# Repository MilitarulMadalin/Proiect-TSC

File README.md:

# InkTime

## Cuprins

1. [Schemă bloc](#1-schemă-bloc)
2. [Bill of Materials (BOM)](#2-bill-of-materials-bom)
3. [Descrierea hardware detaliată](#3-descrierea-hardware-detaliată)
4. [Mapare pini nRF52840](#4-mapare-pini-nrf52840)
5. [Design log](#5-decizii-de-design)

---

## 1. Schemă bloc

```
                  +--------------+      +-------------+
                  |   E-Paper    |      |    LiPo     |
                  |  Drive Circ. |      |   Charger   +
                  +------+-------+      +------+------+
                         |                     |
                         | EPD_PINS            | I2C, PMIC_INT       +-----------+
                         v                     |                     |   Fuel    |
  +-----------+   +--------------+             |            I2C      |   Gauge   |
  |  E-Paper  |<--+   E-Paper    |             |        +----------->|           |
  |   1.5"    |   |    Conn.     |             |        |            +-----------+
  +-----------+   +------+-------+             |        |
                         |                     |        |            +-----------+
                         |  SPI                |        |            |   USB-C   |
                         v                     v        |            |    J4     |
                  +----------------------------+--------+------+     +-----+-----+
                  |                                            |           |
                  |              nRF52840   (U1)               |<----------+
                  |                                            |  D+, D-
                  |                                            |<--------+
                  +--+--------+--------+--------+------+-------+         |
                     |        |        |        |      |                 |
                     | I2C    | I2C    | ANT1   | SWD  | 3xGPIO          | D+, D-
                     |        | HAPT.  |        |      |                 |
                     v        | EN     v        v      v           +-----+-----+
                  +-------+   |   +--------+ +-----+ +---------+   |    ESD    |
                  |  IMU  |   |   | Antena | | SWD | | Butoane |   | Protection|
                  |BMA423 |   |   |  2.4   | | J2  | +---------+   +-----------+
                  +-------+   |   +--------+ +-----+
                              v
                          +-------+
                          |Haptic |
                          |DRV2605|
                          +-------+
```

---

## 2. Bill of Materials (BOM)

| Desig. (ref.)                                                                  | Valoare / Part Number          | Funcție în circuit                           | Pachet        | Cant. | JLCPCB                                           | Datasheet                                                                                         |
|--------------------------------------------------------------------------------|--------------------------------|----------------------------------------------|---------------|-------|--------------------------------------------------|---------------------------------------------------------------------------------------------------|
| U1                                                                             | nRF52840-QIAA                  | MCU BLE 5 / 2.4 GHz, Cortex-M4F, 1 MB Flash  | aQFN73        | 1     | [C190794](https://jlcpcb.com/partdetail/C190794) | [PDF](https://infocenter.nordicsemi.com/pdf/nRF52840_PS_v1.7.pdf)                                 |
| IC1                                                                            | BQ25180YBGR                    | Încărcător LiPo 1-cell, programabil I2C      | DSBGA-8 0.4mm | 1     | [C965556](https://jlcpcb.com/partdetail/C965556) | [PDF](https://www.ti.com/lit/ds/symlink/bq25180.pdf)                                              |
| U3                                                                             | MAX17048G+T10                  | Fuel gauge ModelGauge 1-cell, I2C            | TDFN-8        | 1     | [C129977](https://jlcpcb.com/partdetail/C129977) | [PDF](https://www.analog.com/media/en/technical-documentation/data-sheets/MAX17048-MAX17049.pdf) |
| IC9                                                                            | RT6160AWSC                     | Buck-Boost 3V3, 2A (rail principal)          | WL-CSP-15     | 1     | [C58559](https://jlcpcb.com/partdetail/C58559)   | [PDF](https://www.richtek.com/assets/product_file/RT6160A/DS6160A-02.pdf)                         |
| IC3                                                                            | BMA423                         | Accelerometru 3-axis, step counter, wrist-tilt | LGA-12      | 1     | [C553690](https://jlcpcb.com/partdetail/C553690) | [PDF](https://www.bosch-sensortec.com/media/boschsensortec/downloads/datasheets/bst-bma423-ds000.pdf) |
| IC2                                                                            | DRV2605YZFR                    | Driver haptic ERM/LRA, 123 efecte, I2C       | DSBGA-9       | 1     | [C92482](https://jlcpcb.com/partdetail/C92482)   | [PDF](https://www.ti.com/lit/ds/symlink/drv2605.pdf)                                              |
| Q1                                                                             | DMG2305UX-7 (20V/4.2A)         | P-MOSFET load-switch rail EPD                | SOT-23        | 1     | [C114005](https://jlcpcb.com/partdetail/C114005) | [PDF](https://www.diodes.com/assets/Datasheets/DMG2305UX.pdf)                                     |
| Q3                                                                             | SI1308EDL-T1-GE3               | N-MOSFET pentru boost charge-pump EPD        | SOT-23        | 1     | [C294574](https://jlcpcb.com/partdetail/C294574) | [PDF](https://www.vishay.com/docs/66632/si1308edl.pdf)                                            |
| D3                                                                             | USBLC6-2SC6Y                   | TVS diode array, protecție ESD pe USB D±     | SOT-23-6      | 1     | [C7519](https://jlcpcb.com/partdetail/C7519)     | [PDF](https://www.st.com/resource/en/datasheet/usblc6-2.pdf)                                      |
| D2, D4, D5                                                                     | MBR0530                        | Diodă Schottky 30V pentru charge-pump EPD    | SOD-123       | 3     | [C131850](https://jlcpcb.com/partdetail/C131850) | [PDF](https://www.onsemi.com/pdf/datasheet/mbr0520-d.pdf)                                         |
| ANT1                                                                           | 2450AT18B100E                  | Antenă ceramică chip 2.4 GHz, Johanson       | 3216          | 1     | [C76907](https://jlcpcb.com/partdetail/C76907)   | [PDF](https://www.johansontechnology.com/datasheets/2450AT18B100E.pdf)                            |
| X1                                                                             | NX2016SA 32 MHz ±10 ppm        | Cristal HF pentru radio și CPU               | 2016          | 1     | [C255982](https://jlcpcb.com/partdetail/C255982) | [PDF](https://www.ndk.com/images/products/catalog/c_NX2016SA-STD-CRA-2_e.pdf)                     |
| X2                                                                             | ABS07-120 32.768 kHz           | Cristal LF pentru RTC (low-power)            | 3215          | 1     | [C32346](https://jlcpcb.com/partdetail/C32346)   | [PDF](https://abracon.com/Resonators/abs07-120.pdf)                                               |
| L1                                                                             | 3.9 nH                         | RF match filtru π — inductor serie antenă    | 0402          | 1     | [C1789](https://jlcpcb.com/partdetail/C1789)     | —                                                                                                 |
| L3                                                                             | 15 nH                          | RF match filtru π — inductor paralel          | 0402          | 1     | [C1794](https://jlcpcb.com/partdetail/C1794)     | —                                                                                                 |
| L2                                                                             | 10 µH                          | DCDC intern nRF52840 (pin DCC)               | 0402          | 1     | [C1046](https://jlcpcb.com/partdetail/C1046)     | —                                                                                                 |
| L5                                                                             | WE-TPC 744043680, 68 µH        | Boost e-paper (rail VGH / VGL)                | 4828          | 1     | [C492815](https://jlcpcb.com/partdetail/C492815) | [PDF](https://www.we-online.com/catalog/datasheet/744043680.pdf)                                  |
| L7                                                                             | FTC252012SR47MBCA, 0.47 µH     | Inductor putere pentru RT6160                 | 2520          | 1     | [C123046](https://jlcpcb.com/partdetail/C123046) | —                                                                                                 |
| J4                                                                             | KH-TYPE-C-16P                  | Conector USB-C receptacle (16 pini)           | SMT           | 1     | [C165948](https://jlcpcb.com/partdetail/C165948) | —                                                                                                 |
| J1                                                                             | Molex 503480-2400              | Conector baterie LiPo, 2-pin pitch 1.5 mm     | SMT           | 1     | [C518439](https://jlcpcb.com/partdetail/C518439) | [PDF](https://www.molex.com/pdm_docs/sd/5034802400_sd.pdf)                                        |
| J2                                                                             | TC2030-IDC (Tag-Connect)       | Footprint debug SWD (pogo-pins, fără receptacle) | —         | 1     | (doar footprint)                                 | [PDF](https://www.tag-connect.com/wp-content/uploads/bsk-pdf-manager/TC2030-IDC.pdf)              |
| SW_UP, SW_DN, SW_ENT                                                           | EVP-AKE31A                     | Buton tactil side-push 4.5×3.5 mm             | SMT           | 3     | [C719888](https://jlcpcb.com/partdetail/C719888) | [PDF](https://industrial.panasonic.com/cdbs/www-data/pdf/ATV0000/ATV0000CE11.pdf)                 |
| C11, C12                                                                       | 100 nF / 10V (X7R)             | Decuplare locală IC-uri digitale             | 0201          | 2     | [C106250](https://jlcpcb.com/partdetail/C106250) | —                                                                                                 |
| C5, C7, C8                                                                     | 100 µF / 6.3V                  | Bulk buck-boost RT6160                       | 0201          | 3     | [C19702](https://jlcpcb.com/partdetail/C19702)   | —                                                                                                 |
| C19                                                                            | 100 µF / 6.3V                  | Bulk rail VBAT                               | 0201          | 1     | [C19702](https://jlcpcb.com/partdetail/C19702)   | —                                                                                                 |
| C6, C14, C20, C21                                                              | 4.7 µF / 10V (X7R)             | Decuplare nRF (DEC*)                         | 0201          | 4     | [C19666](https://jlcpcb.com/partdetail/C19666)   | —                                                                                                 |
| C15                                                                            | 1.0 µF / 10V                   | Decuplare VREG nRF                           | 0201          | 1     | [C15849](https://jlcpcb.com/partdetail/C15849)   | —                                                                                                 |
| C39                                                                            | 10 µF / 6.3V                   | Bulk IC1 (charger)                           | 0201          | 1     | [C15850](https://jlcpcb.com/partdetail/C15850)   | —                                                                                                 |
| C43                                                                            | 4.7 µF                         | Intrare IC2 (driver haptic)                  | 0201          | 1     | [C19666](https://jlcpcb.com/partdetail/C19666)   | —                                                                                                 |
| C1-EP-DR, C24                                                                  | 10 µF                          | Filtre intrare driver EPD / RT6160           | 0201          | 2     | [C15850](https://jlcpcb.com/partdetail/C15850)   | —                                                                                                 |
| C2-EP-DR                                                                       | 4.7 µF / 25V                   | Bulk intrare boost EPD                       | 0201          | 1     | [C19666](https://jlcpcb.com/partdetail/C19666)   | —                                                                                                 |
| C25, C33                                                                       | 22 µF                          | Ieșire RT6160 (3V3)                          | 0201          | 2     | [C45783](https://jlcpcb.com/partdetail/C45783)   | —                                                                                                 |
| C17, C18                                                                       | 12 µF                          | Filtre DCDC intern nRF                       | 0201          | 2     | [C162698](https://jlcpcb.com/partdetail/C162698) | —                                                                                                 |
| C16                                                                            | 47 nF                          | Filtru control-loop RT6160                   | 0201          | 1     | [C113010](https://jlcpcb.com/partdetail/C113010) | —                                                                                                 |
| C9                                                                             | 820 pF                         | Decuplare DEC6 nRF                           | 0201          | 1     | [C1603](https://jlcpcb.com/partdetail/C1603)     | —                                                                                                 |
| C1, C2                                                                         | 12 pF (NP0 / C0G)              | Load-caps pentru X1 (32 MHz)                 | 0201          | 2     | [C1570](https://jlcpcb.com/partdetail/C1570)     | —                                                                                                 |
| C3, C4                                                                         | 1 pF                           | RF match (π) — shunt                         | 0201          | 2     | [C1552](https://jlcpcb.com/partdetail/C1552)     | —                                                                                                 |
| C10, C13, C22                                                                  | N.C. (Not Connected)           | Rezervate — neplasate la fabricație          | 0201          | 3     | (nu se lipește)                                  | —                                                                                                 |
| C23, C27, C29, C30, C31, C32, C34, C37, C38, C42                               | GRM011R60J152KE01L, 1.5 nF     | Filtre RF / bypass high-freq                 | 0201          | 10    | [C400827](https://jlcpcb.com/partdetail/C400827) | [PDF](https://www.murata.com/en-us/products/productdata/8796840689694/GCM155C71A225KE36-01A.pdf)  |
| EPD_C1, EPD_C2, EPD_C6, EPD_C7, EPD_C8, EPD_C9, EPD_C10, EPD_C11, EPD_C12      | 1 µF / 50V (X7R)               | Flying caps charge-pump pentru VGH/VGL       | 0201          | 9     | [C105948](https://jlcpcb.com/partdetail/C105948) | —                                                                                                 |
| EPD_C5                                                                         | 0.1 µF / 50V                   | Decuplare driver EPD                          | 0201          | 1     | [C14663](https://jlcpcb.com/partdetail/C14663)   | —                                                                                                 |
| R1_USB, R2_USB                                                                 | 5.1 kΩ 1% (CC1 / CC2)           | Pull-down USB-C — configurare device UFP     | 0201          | 2     | [C98220](https://jlcpcb.com/partdetail/C98220)   | —                                                                                                 |
| R1_EP_DR, R2_EP_DR                                                             | 10 kΩ 1%                       | Divider / gate pull pentru boost EPD         | 0201          | 2     | [C25744](https://jlcpcb.com/partdetail/C25744)   | —                                                                                                 |
| R_PWR_EPD, R_TYPE_SEL                                                          | 10 kΩ 1%                       | Selector tip panou EPD / enable rail         | 0201          | 2     | [C25744](https://jlcpcb.com/partdetail/C25744)   | —                                                                                                 |
| R2, R3, R4                                                                     | 0 Ω                            | Jumperi / pull-uri I2C (SDA, SCL, ALERT)     | 0201          | 3     | [C17168](https://jlcpcb.com/partdetail/C17168)   | —                                                                                                 |
| R5, R7, R8                                                                     | 10 kΩ 1%                       | Pull-up butoane SW_UP, SW_DN, SW_ENT         | 0201          | 3     | [C25744](https://jlcpcb.com/partdetail/C25744)   | —                                                                                                 |
| R9                                                                             | 10 kΩ 1%                       | MR (TS / mode-select) pe BQ25180             | 0201          | 1     | [C25744](https://jlcpcb.com/partdetail/C25744)   | —                                                                                                 |
| R17, R18                                                                       | 3.3 kΩ 1%                      | Feedback / setare tensiune RT6160            | 0201          | 2     | [C22975](https://jlcpcb.com/partdetail/C22975)   | —                                                                                                 |
| TP_3V3, TP_3.3V, TP_VREG, TP_VBAT, TP_BAT_GND, TP_GND, TP_RESET, TP_SDA, TP_SCL, TP_SWDCLK, TP_SWDIO, TP_SWO, TP_ON, TP_OP | Pad 20 mil               | Puncte de test pentru măsurători / debug     | 20R pad       | 14    | (doar footprint)                                 | —                                                                                                 |
| SJ1                                                                            | Solder jumper                  | Select hardware (bootloader / mod)            | 0201 jumper   | 1     | (doar footprint)                                 | —                                                                                                 |

### Off-board

| Componentă          | Valoare / Model                      | Legătură                                   |
|---------------------|--------------------------------------|--------------------------------------------|
| Baterie             | LiPo 483450, 3.7V, 2400 mAh          | Conector J1 (Molex 503480-2400)            |
| Panou e-paper       | GDEW0154M09, 1.54" 200×200 px, SPI   | Conector FPC 24 pini (nu e pe placă — se leagă prin cablaj) |
| Motor vibrație      | ERM 10×2.7 mm, 3V nominal            | Pini OUT+ / OUT− ai DRV2605                |

---

## 3. Descrierea hardware detaliată

### 3.1. Alimentare

Lanțul de alimentare respectă o arhitectură clasică **charger → baterie → regulator**, adaptată pentru low-power:

1. **Intrare USB-C (J4)** — 5V / max 500 mA. Liniile D+/D− sunt protejate de **USBLC6-2 (D3)**, diodă TVS cu capacitate mică care nu afectează eye-pattern-ul USB 2.0 Full-Speed.
2. **Încărcător BQ25180 (IC1)** — integrează charger liniar 1-cell LiPo cu până la 500 mA, path management, detecție over-voltage 18V și **ship-mode**. Configurabil pe I2C: curent de încărcare, prag de terminare, temperatură. Pinul **INT** este conectat la nRF pentru evenimente.
3. **Baterie LiPo 2400 mAh** conectată la J1. Pinul TS/MR al BQ25180 nu folosește termistor.
4. **Fuel gauge MAX17048 (U3)** — măsoară direct tensiunea bateriei cu algoritmul **ModelGauge**, oferind SoC și rata de descărcare. Pinul ALERT este rutat la nRF pentru notificări de low-battery.
5. **Buck-Boost RT6160 (IC9)** — convertor **step-up/step-down** la **3V3 fix**, eficiență până la 95%. Alegerea unui buck-boost e critică: o baterie LiPo ajunge la ~3.0V la descărcare, iar un LDO ar avea dropout, în timp ce un buck pur nu ar putea menține 3V3 când bateria e sub acest nivel. RT6160 oferă continuitate până la ~2.5V cu regulare menținută.
6. **Load-switch Q1 (DMG2305UX-7)** — P-MOSFET care deconectează complet rail-ul boost al e-paper-ului în stand-by.

**Rețeaua RF**: antena ceramică ANT1 e alimentată prin **filtru π** pentru match la 50 Ω și filtrare armonici. Traseul de la pinul **ANT** al nRF la antenă respectă **controlled impedance** 50 Ω.

### 3.2. Microcontroller și clock

**nRF52840** rulează cu două cristale:

- **X1 = 32 MHz (NX2016SA)** pe pinii XC1/XC2, cristal principal pentru radio și HFCLK. Toleranță ≤ 40 ppm.
- **X2 = 32.768 kHz (ABS07)** pe pinii P0.00/XL1, P0.01/XL2, clock low-power pentru RTC și sleep. Toleranță 20 ppm, consum < 1 µA.

Decuplarea rail-urilor interne folosește 4.7 µF + 100 nF + 1 µF + 100 pF conform reference design Nordic. **L4 + L6**împreună cu C14 + C15 + C20 implementează DC/DC intern care reduce consumul cu ~30% față de modul LDO.

### 3.3. Display e-paper

E-paper-ul **GDEW0154M09** are nevoie de patru rail-uri: +15V (VGH), −15V (VGL), +22V (VPP), −20V (VEE). Driver circuit-ul de pe Sheet 2 folosește:

- **Boost cu SI1308 + L5 + MBR0530** care generează VGH/VGL prin charge-pump multi-stage.
- **9× condensatori 1µF/50V** — flying caps pentru stagele charge-pump.

Controlul e pe SPI + semnale discrete: RST, BUSY, D/C, CS. Rail-ul EPD_3V3 se activează doar când se refresh-uiește display-ul; în rest, e-paper-ul menține imaginea fără alimentare.

### 3.4. Senzori și actuatori

- **BMA423 (IC3)** — accelerometru 3-axis 12-bit cu engine de pași, detecție tap/double-tap și wrist-tilt. Întreruperi: INT1, INT2. Interfața I2C, adresa 0x19.
- **DRV2605 (IC2)** — driver haptic pentru motoare ERM sau LRA. Conține **librărie pre-programată cu 123 efecte**, plus mod real-time. Activat prin HAPTIC_EN pentru a elimina complet consumul în idle. Bobina motorului e conectată la pinii OUT+/OUT−.

### 3.5. Butoane și debug

Cele 3 butoane sunt conectate GPIO cu GND, cu pull-up intern activat software. **Fără debounce hardware** , se face în firmware.

Conectorul **TC2030-IDC (J2)** e un footprint 6-pin fără receptacle fizic, debugger-ul are pogo-pins care fac contact direct pe PCB, economisind componenta și spațiu. Semnale: SWDIO, SWDCLK, SWO, RESET, 3V3, GND.

---

## 4. Mapare pini nRF52840

Mapare extrasă din schematic (InkTime v6, Sheet 1 + Sheet 2):

| Pin nRF52840    | Nume net       | Funcție firmware                | Destinație periferic          |
|-----------------|----------------|---------------------------------|-------------------------------|
| **Alimentare**  |                |                                 |                               |
| VDD / VDDH      | 3V3            | Alimentare digital              | Rail 3V3 (de la RT6160)        |
| VBUS            | VBUS           | Detecție USB plug-in            | USB 5V                         |
| DEC1..DEC6      | DEC*           | Decuplare internă               | Local 100 nF × 6               |
| DCC / DCCH      | LX1 / LX2      | DC-DC intern (SMPS)             | L4 + L6 (10 µH) + filtre      |
| **Clock**       |                |                                 |                               |
| P0.00 / XL1     | XL1            | Cristal RTC 32.768 kHz          | X2                             |
| P0.01 / XL2     | XL2            | Cristal RTC 32.768 kHz          | X2                             |
| XC1 / XC2       | XC1 / XC2      | Cristal HF 32 MHz               | X1                             |
| **Radio**       |                |                                 |                               |
| ANT             | RF             | Ieșire RF                       | filtru π → ANT1                |
| **USB**         |                |                                 |                               |
| D+              | D+             | USB 2.0 Full-Speed              | J4 (prin USBLC6-2)            |
| D-              | D-             | USB 2.0 Full-Speed              | J4 (prin USBLC6-2)            |
| **Debug**       |                |                                 |                               |
| SWDCLK          | SWDCLK         | Clock debug                     | J2 pin 4                       |
| SWDIO           | SWDIO          | Data debug                      | J2 pin 2                       |
| P0.18 / nRESET  | RESET          | Reset hardware                  | J2 pin 5 + TP_RESET           |
| **SPI (TWIM1)** — e-paper |      |                                 |                               |
| P0.13           | EPD_SCK / SCK  | Clock SPI                       | FPC pin 5                      |
| P0.14           | EPD_MOSI / MOSI| Data SPI master→slave           | FPC pin 4                      |
| P0.15           | EPD_CS         | Chip-select                     | FPC pin 6                      |
| P0.16           | EPD_DC         | Data / Command                  | FPC pin 7                      |
| P0.17           | EPD_RST        | Reset display                   | FPC pin 8                      |
| P0.19           | EPD_BUSY       | Busy-in (drive done)            | FPC pin 9                      |
| **I2C (TWIM0)** — senzori |      |                                 |                               |
| P0.24           | SDA            | I2C data                        | BMA423 · DRV2605 · MAX17048 · BQ25180 |
| P0.25           | SCL            | I2C clock                       | BMA423 · DRV2605 · MAX17048 · BQ25180 |
| **Întreruperi** |                |                                 |                               |
| P0.22           | IMU_INT1       | IMU: pași / tap                 | BMA423 pin 5                   |
| P0.23           | IMU_INT2       | IMU: wake-up                    | BMA423 pin 6                   |
| P0.20           | ALERT          | Fuel gauge low-bat              | MAX17048 pin 5                 |
| P0.21           | PMIC_INT       | Charger events                  | BQ25180 pin A1                 |
| **Butoane**     |                |                                 |                               |
| P0.04           | SW_UP          | Buton sus                       | SW_UP (push-to-GND)            |
| P0.05           | SW_DN          | Buton jos                       | SW_DN (push-to-GND)            |
| P0.06           | SW_ENT         | Buton enter                     | SW_ENT (push-to-GND)           |
| **Control**     |                |                                 |                               |
| P0.26           | HAPTIC_EN      | Enable DRV2605 + boost EPD     | IC2 pin EN / Q3 gate          |
| P0.27           | EPD_PWR        | Load-switch panou e-paper       | Q1 gate                        |

---

## 5. Decizii de design

- **Utilizarea componentelor SMD în capsule mici** Am ales respectarea strictă a dimensiunilor impuse (0201 pentru rezistențe și condensatoare ≤100nF, respectiv 0402 pentru valori mai mari) pentru a reduce dimensiunea totală a PCB-ului. Această alegere contribuie la integrarea mai ușoară în carcasă și la un design compact, esențial pentru dispozitive portabile.
- **Amplasarea componentelor doar pe layer-ul TOP** Toate componentele au fost plasate pe TOP pentru a simplifica procesul de asamblare și pentru a evita costuri suplimentare asociate montajului pe ambele fețe. În plus, această abordare reduce riscul de erori mecanice și facilitează inspecția vizuală.
- **Excluderea planului de masă sub antenă** Zona de sub antenă a fost complet decuplată de planul de masă și nu au fost rutate semnale acolo. Aceasta previne detunarea antenei și pierderile de eficiență, asigurând performanță RF optimă.
- **Silkscreen minimalist și lizibil** Am inclus doar denumirile componentelor pentru a evita aglomerarea vizuală. Un silkscreen curat ajută la identificarea rapidă a componentelor și îmbunătățește mentenanța.
- **Utilizarea unui PCB cu 4 layere** Am ales o structură pe 4 layere (TOP, GND plane, POWER plane, BOTTOM) pentru a îmbunătăți semnificativ integritatea semnalului și stabilitatea alimentării.

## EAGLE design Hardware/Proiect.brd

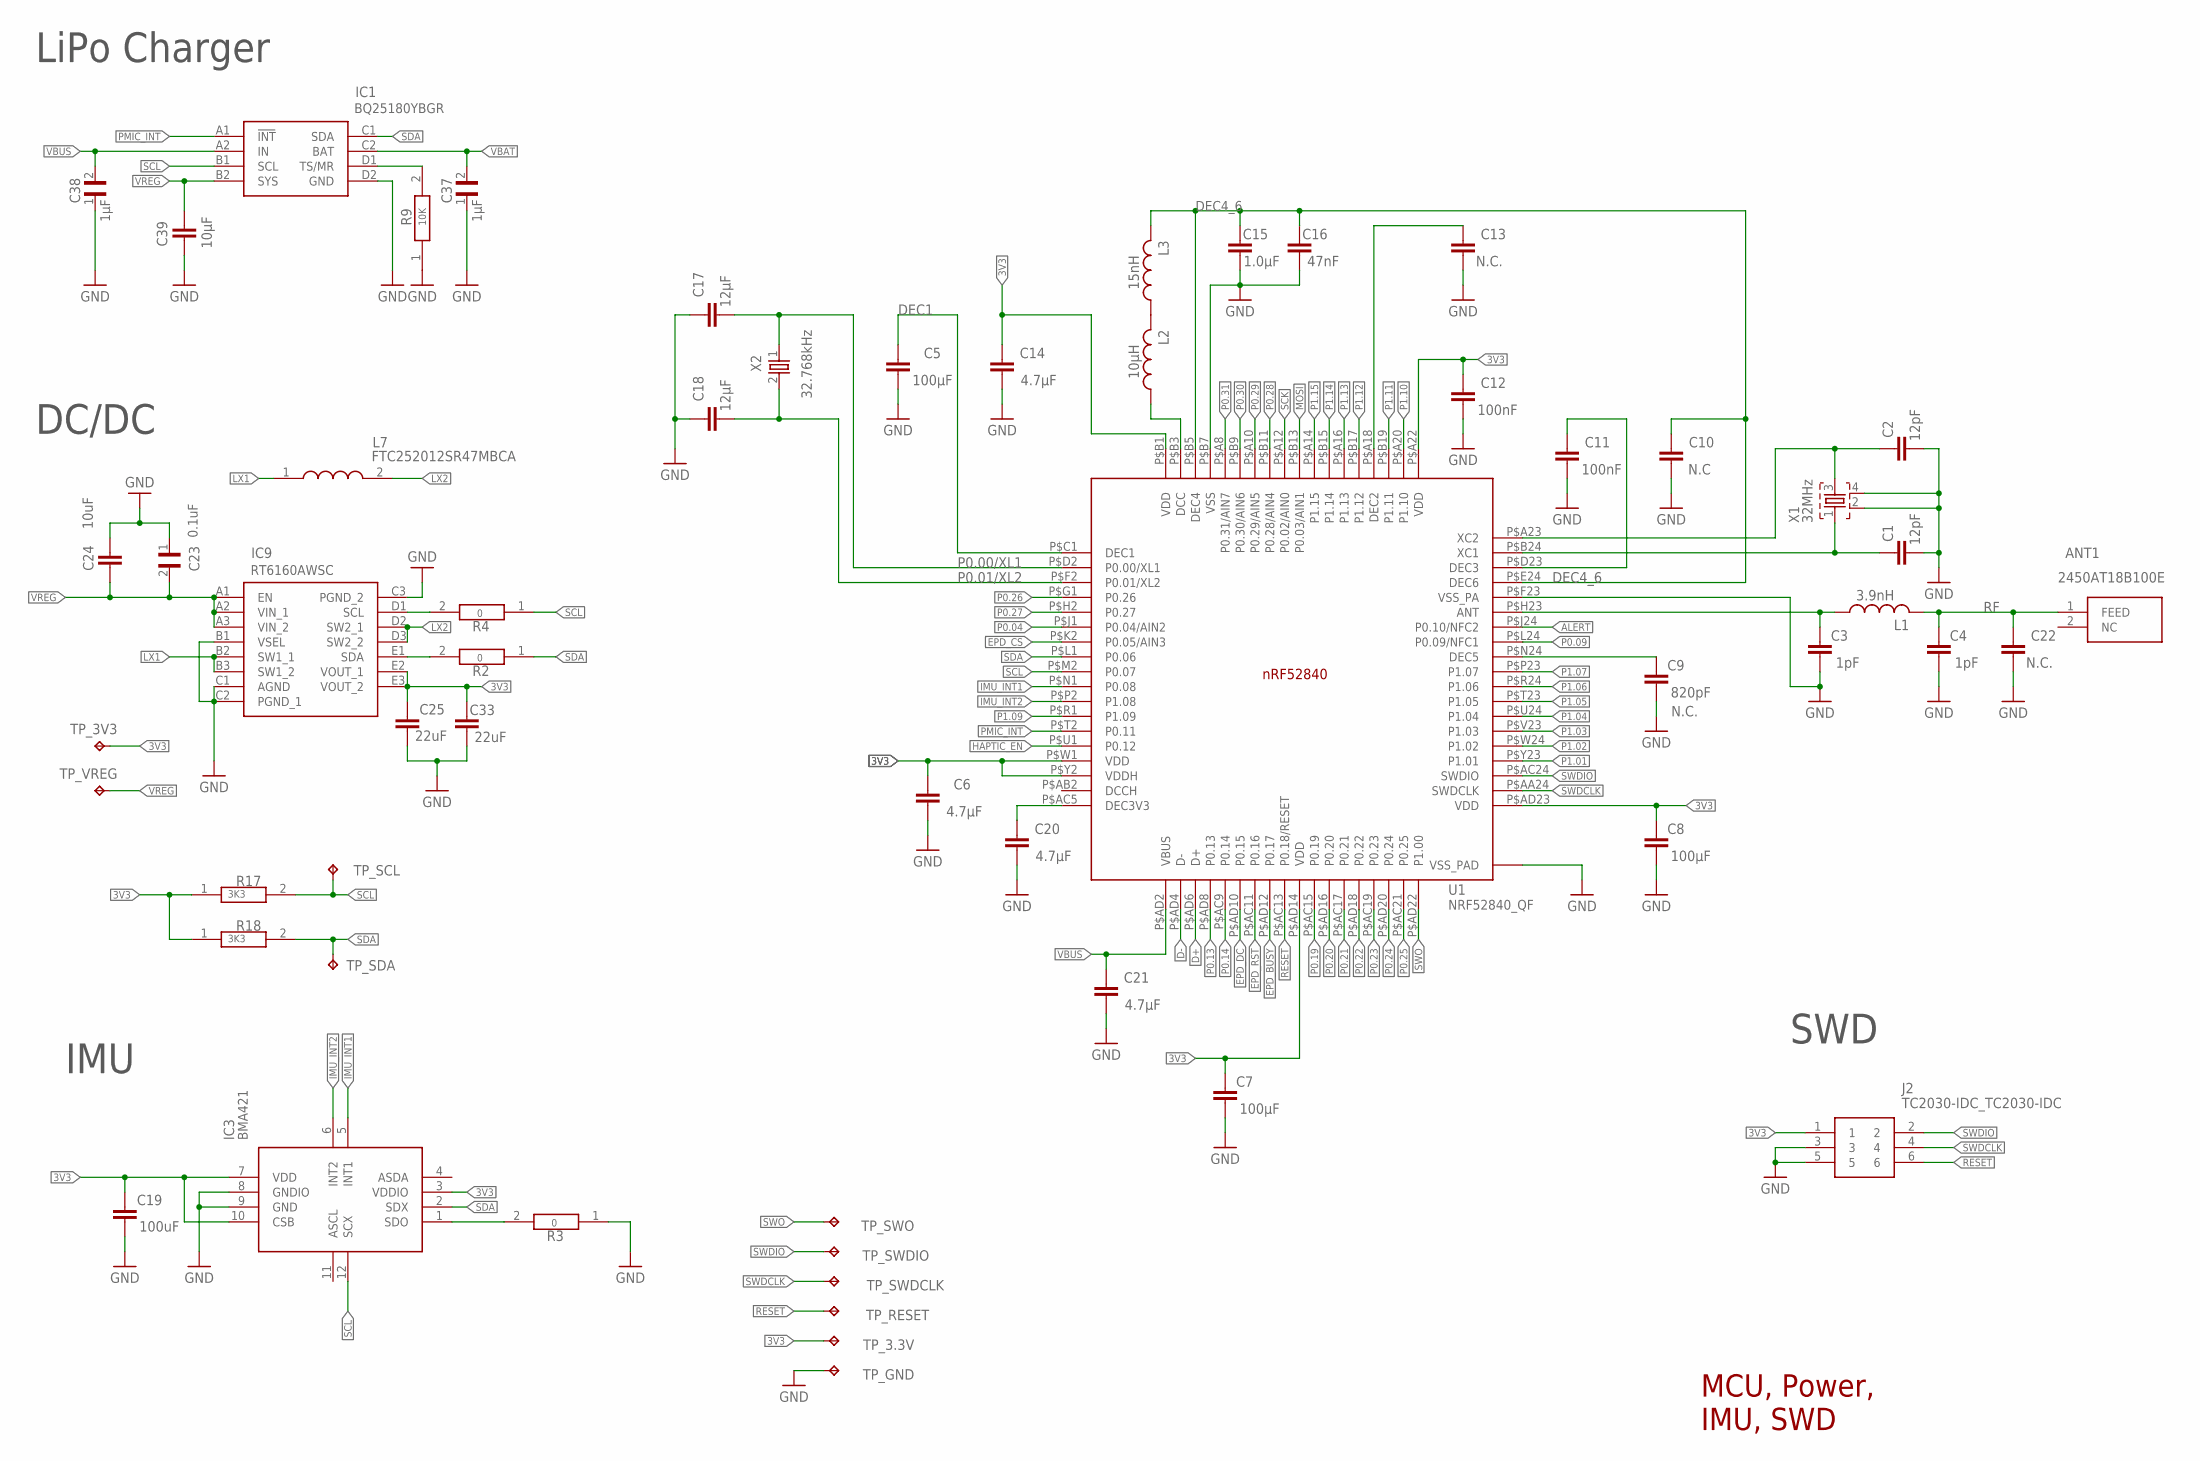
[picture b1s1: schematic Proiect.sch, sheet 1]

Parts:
ANT1: 2450AT18B100E_2450AT18B100E; 2450AT18B100E_ANTC3216X140N
C1, C2: 12pF; NORDIC_NRF_3_RESC0201_L
C3, C4: 1pF; NORDIC_NRF_3_RESC0201_L
C5, C7, C8: 100µF; NORDIC_NRF_3_RESC0201_L
C6, C14, C20, C21: 4.7µF; NORDIC_NRF_3_RESC0201_L
C9: 820pF; NORDIC_NRF_3_RESC0201_L
C10: N.C; NORDIC_NRF_3_RESC0201_L
C11, C12: 100nF; NORDIC_NRF_3_RESC0201_L
C13, C22: N.C.; NORDIC_NRF_3_RESC0201_L
C15: 1.0µF; NORDIC_NRF_3_RESC0201_L
C16: 47nF; NORDIC_NRF_3_RESC0201_L
C17, C18: 12µF; NORDIC_NRF_3_RESC0201_L
C19: 100uF; NORDIC_NRF_3_RESC0201_L
C23, C37, C38: GRM011R60J152KE01L_2_GRM011R60J152KE01L; GRM011R60J152KE01L_2_CAPC0201X13N
C24: 10uF; NORDIC_NRF_3_RESC0201_L
C25, C33: 22uF; NORDIC_NRF_3_RESC0201_L
C39: 10µF; NORDIC_NRF_3_RESC0201_L
IC1: BQ25180YBGR_BQ25180YBGR; BQ25180YBGR_BGA8C40P2X4_100X155X50
IC3: BMA423_BMA423
IC9: RT6160AWSC_RT6160AWSC; RT6160AWSC_BGA15C40P3X5_140X230X60
J2: TC2030-IDC_TC2030-IDC; TC2030-IDC_TC2030IDC
L1: 3.9nH; NORDIC_NRF_2_RESC0402_L
L2: 10µH; NORDIC_NRF_2_RESC0402_L
L3: 15nH; NORDIC_NRF_2_RESC0402_L
L7: MLP2016SR47MT0S1_FTC252012SR47MBCA; MLP2016SR47MT0S1_INDC2016X100N
R2, R3, R4, R9, R17, R18: ERA-1AEB3401C_CPF0201D7K68C1; ERA-1AEB3401C_0201
TP_3.3V, TP_3V3: HECTOR_WATCH_1_TPTP20R; HECTOR_WATCH_1_TP20R
TP_GND: HECTOR_WATCH_1_TPTP20R; HECTOR_WATCH_1_TP20R
TP_RESET: HECTOR_WATCH_1_TPTP20R; HECTOR_WATCH_1_TP20R
TP_SCL: HECTOR_WATCH_1_TPTP20R; HECTOR_WATCH_1_TP20R
TP_SDA: HECTOR_WATCH_1_TPTP20R; HECTOR_WATCH_1_TP20R
TP_SWDCLK: HECTOR_WATCH_1_TPTP20R; HECTOR_WATCH_1_TP20R
TP_SWDIO: HECTOR_WATCH_1_TPTP20R; HECTOR_WATCH_1_TP20R
TP_SWO: HECTOR_WATCH_1_TPTP20R; HECTOR_WATCH_1_TP20R
TP_VREG: HECTOR_WATCH_1_TPTP20R; HECTOR_WATCH_1_TP20R
U1: NORDIC_NRF_4_NRF52840_QF; NORDIC_NRF_4_AQFN50P700X700X85_HS-74N
X1: 32MHz; NORDIC_NRF_BT-XTAL_2016_N
X2: 32.768kHz; NORDIC_NRF_1_XTAL_3215_N

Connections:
3V3: C6.1, C7.1, C8.1, C12.1, C14.1, C19.1, C25.1, C33.1, IC3.3 (VDDIO), IC3.7 (VDD), IC3.10 (CSB), IC9.E2 (VOUT_1), IC9.E3 (VOUT_2), J2.1, R17.1, R18.1, TP_3.3V.TP, TP_3V3.TP, U1.P$A22 (VDD), U1.P$AD14 (VDD), U1.P$AD23 (VDD), U1.P$B1 (VDD), U1.P$W1 (VDD), U1.P$Y2 (VDDH); also elsewhere on the board
ALERT: U1.P$J24 (P0.10/NFC2); also elsewhere on the board
D+: U1.P$AD6 (D+); also elsewhere on the board
D-: U1.P$AD4 (D-); also elsewhere on the board
DEC1: C5.1, U1.P$C1 (DEC1)
DEC4_6: C10.1, C15.1, C16.1, L3.2, U1.P$B5 (DEC4), U1.P$E24 (DEC6)
EPD_BUSY: U1.P$AD12 (P0.17); also elsewhere on the board
EPD_CS: U1.P$K2 (P0.05/AIN3); also elsewhere on the board
EPD_DC: U1.P$AD10 (P0.15); also elsewhere on the board
EPD_RST: U1.P$AC11 (P0.16); also elsewhere on the board
GND: C1.2, C2.2, C3.2, C4.2, C5.2, C6.2, C7.2, C8.2, C9.2, C10.2, C11.2, C12.2, C13.2, C14.2, C15.2, C16.2, C17.1, C18.1, C19.2, C20.2, C21.2, C22.2, C23.1, C24.1, C25.2, C33.2, C37.1, C38.1, C39.2, IC1.D2 (GND), IC3.8 (GNDIO), IC3.9 (GND), IC9.B1 (VSEL), IC9.C1 (AGND), IC9.C2 (PGND_1), IC9.C3 (PGND_2), J2.3, J2.5, R3.1, R9.1, TP_GND.TP, U1.P$74 (VSS_PAD), U1.P$75 (VSS_PAD), U1.P$76 (VSS_PAD), U1.P$77 (VSS_PAD), U1.P$78 (VSS_PAD), U1.P$79 (VSS_PAD), U1.P$80 (VSS_PAD), U1.P$81 (VSS_PAD), U1.P$82 (VSS_PAD), U1.P$83 (VSS_PAD), U1.P$84 (VSS_PAD), U1.P$85 (VSS_PAD), U1.P$86 (VSS_PAD), U1.P$87 (VSS_PAD), U1.P$88 (VSS_PAD), U1.P$89 (VSS_PAD), U1.P$90 (VSS_PAD), U1.P$B7 (VSS), U1.P$F23 (VSS_PA), X1.2, X1.4; also elsewhere on the board
HAPTIC_EN: U1.P$U1 (P0.12); also elsewhere on the board
IMU_INT1: IC3.5 (INT1), U1.P$N1 (P0.08)
IMU_INT2: IC3.6 (INT2), U1.P$P2 (P1.08)
LX1: IC9.B2 (SW1_1), IC9.B3 (SW1_2), L7.1
LX2: IC9.D2 (SW2_1), IC9.D3 (SW2_2), L7.2
MOSI: U1.P$B13 (P0.03/AIN1); also elsewhere on the board
unnamed: IC3.1 (SDO), R3.2
unnamed: IC1.D1 (TS/MR), R9.2
unnamed: IC9.E1 (SDA), R2.2
unnamed: IC9.D1 (SCL), R4.2
unnamed: L2.1, U1.P$B3 (DCC)
unnamed: L2.2, L3.1
unnamed: C13.1, U1.P$A18 (DEC2)
unnamed: C9.1, U1.P$N24 (DEC5)
unnamed: C11.1, U1.P$D23 (DEC3)
unnamed: C3.1, L1.1, U1.P$H23 (ANT)
unnamed: C2.1, U1.P$A23 (XC2), X1.3
unnamed: C1.1, U1.P$B24 (XC1), X1.1
P0.00/XL1: C17.2, U1.P$D2 (P0.00/XL1), X2.1
P0.01/XL2: C18.2, U1.P$F2 (P0.01/XL2), X2.2
P0.04: U1.P$J1 (P0.04/AIN2)
P0.09: U1.P$L24 (P0.09/NFC1)
P0.13: U1.P$AD8 (P0.13); also elsewhere on the board
P0.14: U1.P$AC9 (P0.14); also elsewhere on the board
P0.19: U1.P$AC15 (P0.19)
P0.20: U1.P$AD16 (P0.20)
P0.21: U1.P$AC17 (P0.21)
P0.22: U1.P$AD18 (P0.22)
P0.23: U1.P$AC19 (P0.23)
P0.24: U1.P$AD20 (P0.24)
P0.25: U1.P$AC21 (P0.25)
P0.26: U1.P$G1 (P0.26)
P0.27: U1.P$H2 (P0.27)
P0.28: U1.P$B11 (P0.28/AIN4)
P0.29: U1.P$A10 (P0.29/AIN5)
P0.30: U1.P$B9 (P0.30/AIN6)
P0.31: U1.P$A8 (P0.31/AIN7)
P1.01: U1.P$Y23 (P1.01); also elsewhere on the board
P1.02: U1.P$W24 (P1.02); also elsewhere on the board
P1.03: U1.P$V23 (P1.03)
P1.04: U1.P$U24 (P1.04)
P1.05: U1.P$T23 (P1.05)
P1.06: U1.P$R24 (P1.06)
P1.07: U1.P$P23 (P1.07)
P1.09: U1.P$R1 (P1.09)
P1.10: U1.P$A20 (P1.10)
P1.11: U1.P$B19 (P1.11)
P1.12: U1.P$B17 (P1.12)
P1.13: U1.P$A16 (P1.13)
P1.14: U1.P$B15 (P1.14)
P1.15: U1.P$A14 (P1.15)
PMIC_INT: IC1.A1 (!INT), U1.P$T2 (P0.11)
RESET: J2.6, TP_RESET.TP, U1.P$AC13 (P0.18/RESET)
RF: ANT1.1 (FEED), C4.1, C22.1, L1.2
SCK: U1.P$A12 (P0.02/AIN0); also elsewhere on the board
SCL: IC1.B1 (SCL), IC3.12 (SCX), R4.1, R17.2, TP_SCL.TP, U1.P$M2 (P0.07); also elsewhere on the board
SDA: IC1.C1 (SDA), IC3.2 (SDX), R2.1, R18.2, TP_SDA.TP, U1.P$L1 (P0.06); also elsewhere on the board
SWDCLK: J2.4, TP_SWDCLK.TP, U1.P$AA24 (SWDCLK)
SWDIO: J2.2, TP_SWDIO.TP, U1.P$AC24 (SWDIO)
SWO: TP_SWO.TP, U1.P$AD22 (P1.00)
VBAT: C37.2, IC1.C2 (BAT); also elsewhere on the board
VBUS: C21.1, C38.2, IC1.A2 (IN), U1.P$AD2 (VBUS); also elsewhere on the board
VBUS/2.6D1: C20.1, U1.P$AC5 (DEC3V3)
VREG: C23.2, C24.2, C39.1, IC1.B2 (SYS), IC9.A1 (EN), IC9.A2 (VIN_1), IC9.A3 (VIN_2), TP_VREG.TP

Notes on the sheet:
LiPo Charger
MCU, Power, IMU, SWD
DC/DC
IMU
SWD

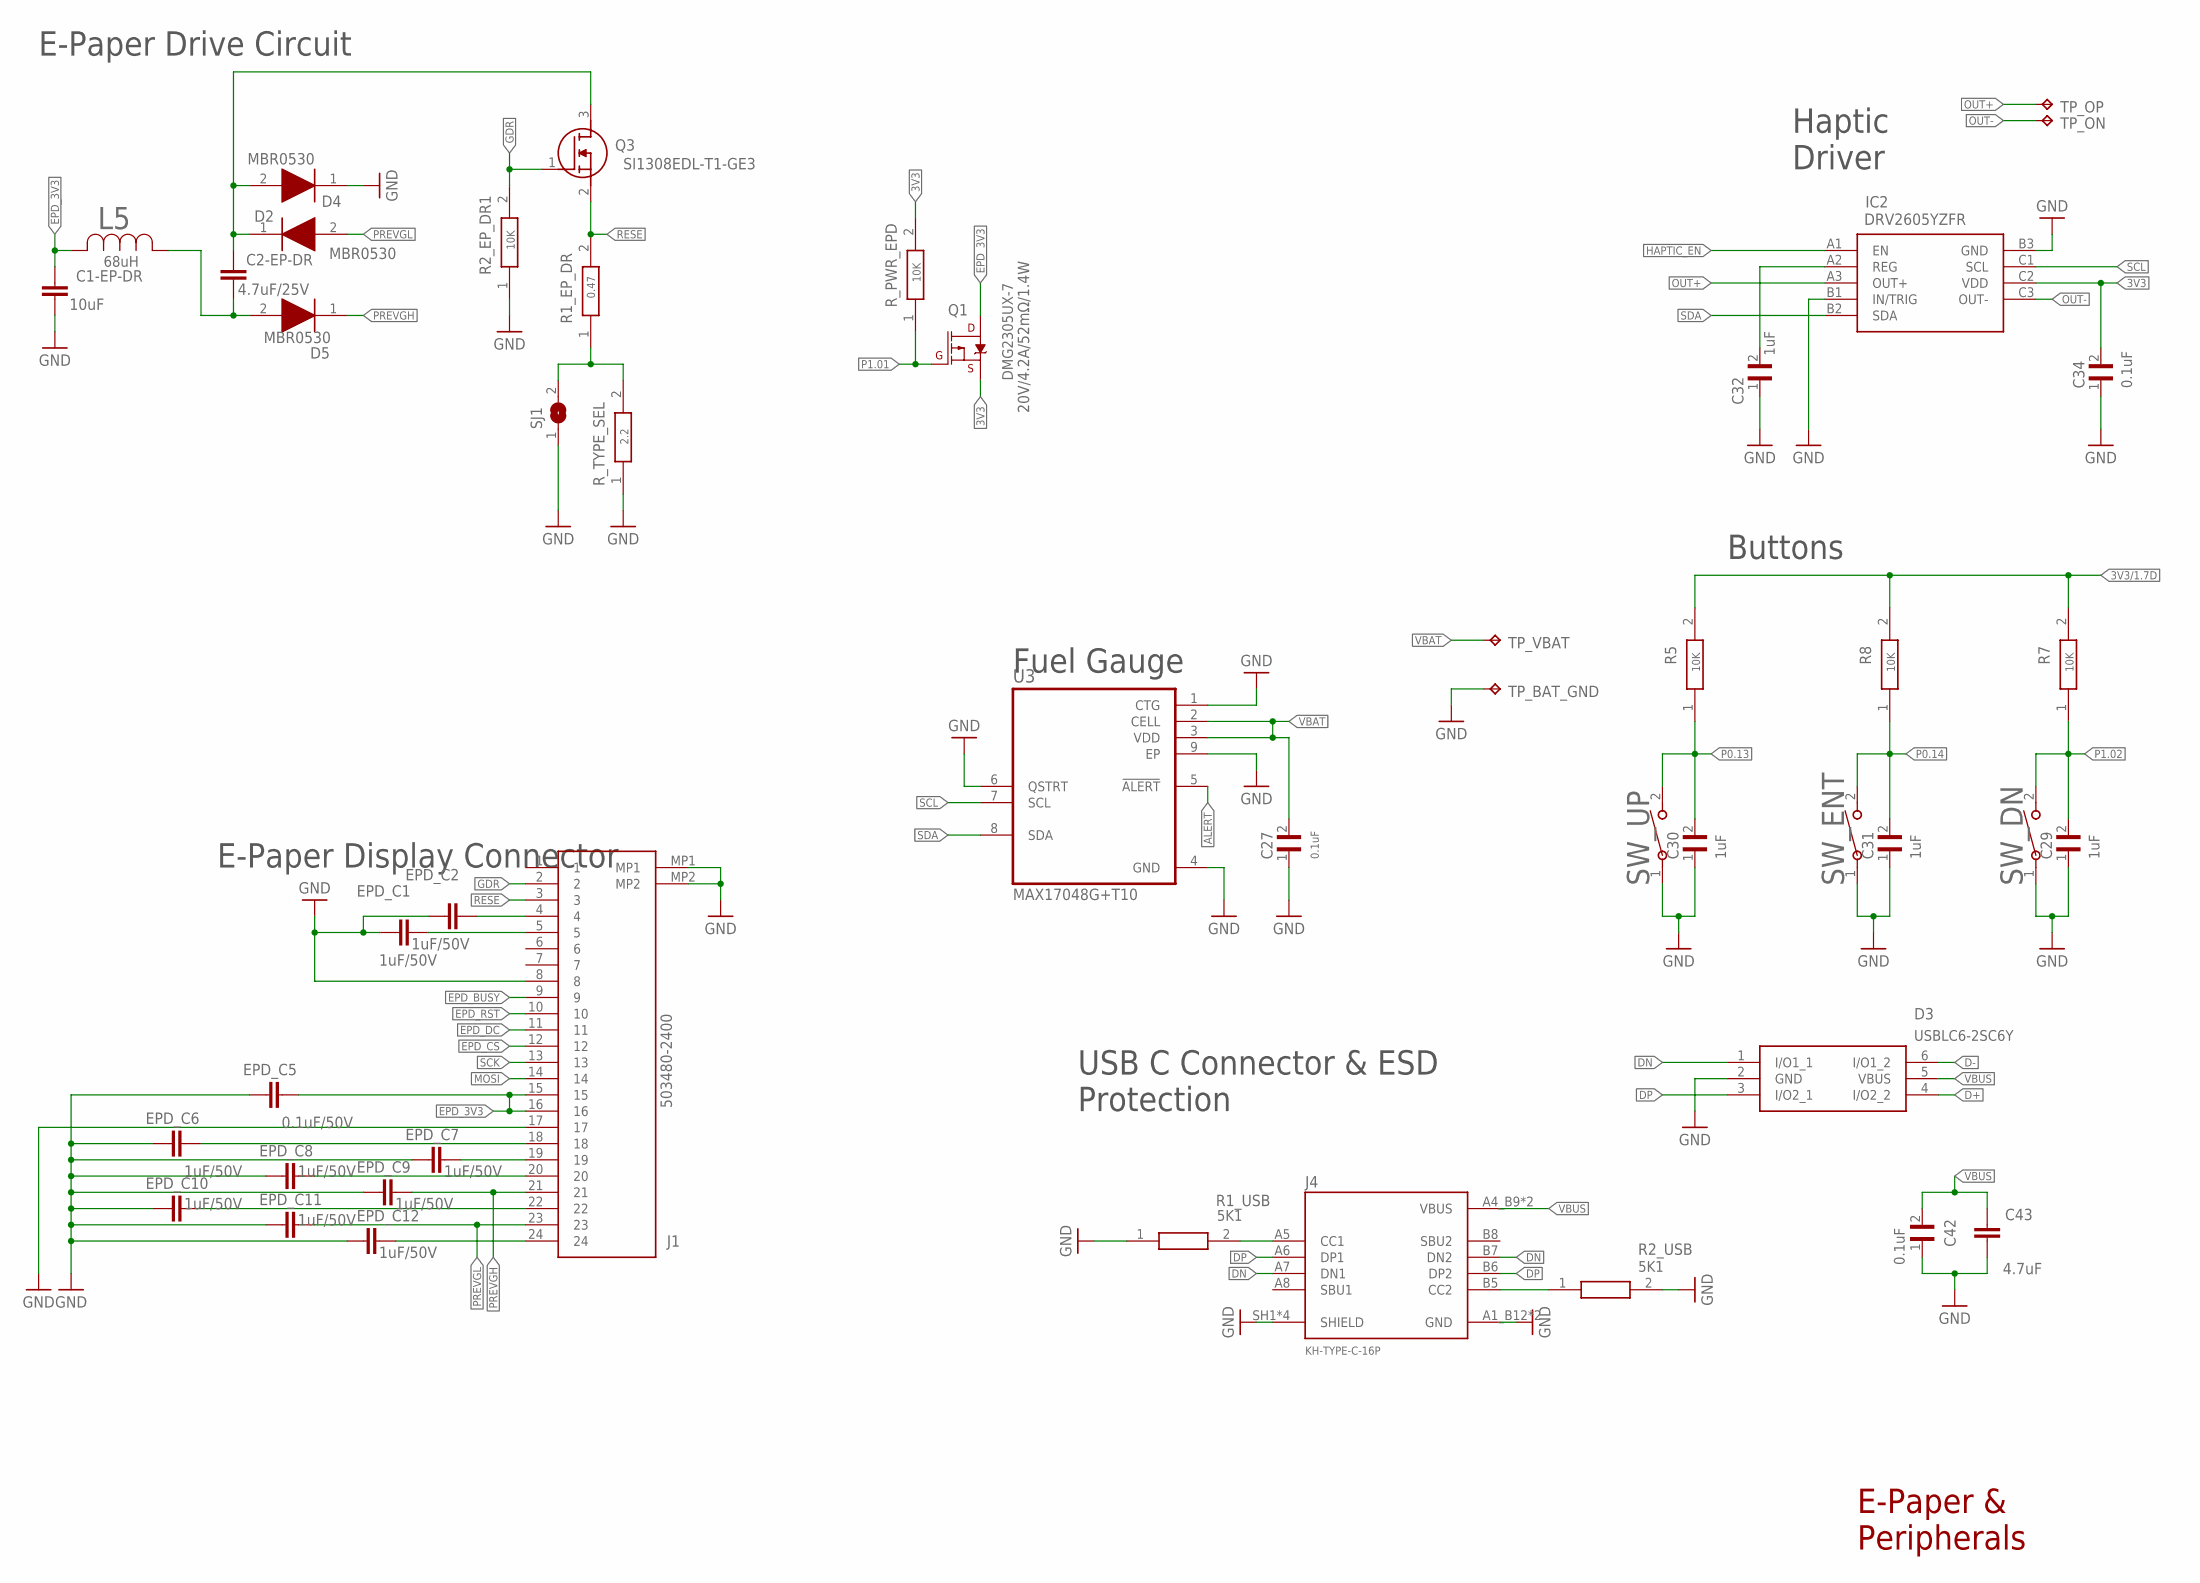
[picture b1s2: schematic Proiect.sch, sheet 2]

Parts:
C1-EP-DR: 10uF; NORDIC_NRF_3_RESC0201_L
C2-EP-DR: 4.7uF/25V; NORDIC_NRF_3_RESC0201_L
C27, C29, C30, C31, C32, C34, C42: GRM011R60J152KE01L_2_GRM011R60J152KE01L; GRM011R60J152KE01L_2_CAPC0201X13N
C43: 4.7uF; NORDIC_NRF_3_RESC0201_L
D2, D4, D5: ESP32_C6_LIBRARY_5_MBR0530; ESP32_C6_LIBRARY_5_SOD3716X135N
D3: ESP32_C6_LIBRARY_3_USBLC6-2SC6Y; ESP32_C6_LIBRARY_3_SOT95P280X145-6N
EPD_C1, EPD_C2, EPD_C6, EPD_C7, EPD_C8, EPD_C9, EPD_C10, EPD_C11, EPD_C12: 1uF/50V; NORDIC_NRF_3_RESC0201_L
EPD_C5: 0.1uF/50V; NORDIC_NRF_3_RESC0201_L
IC2: DRV2605YZFR_DRV2605YZFR; DRV2605YZFR_BGA9C50P3X3_144X144X62
J1: 503480-2400_503480-2400; 503480-2400_5034802400
J4: KH-TYPE-C-16P_KH-TYPE-C-16P; KH-TYPE-C-16P_KINGHELM_KH-TYPE-C-16P
L5: ESP32_C6_LIBRARY_2_744043680IND_4828-WE-TPC_WRE; ESP32_C6_LIBRARY_2_IND_4828-WE-TPC_WRE
Q1: 20V/4.2A/52mΩ/1.4W; ESP32_C6_LIBRARY_4_ESP32_C6_LIBRARY_4_ESP32_C6_LIBRARY_4_ES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
Q3: ESP32_C6_LIBRARY_6_SI1308EDL-T1-GE3; ESP32_C6_LIBRARY_6_SOT65P210X110-3N
R1_EP_DR, R1_USB, R2_EP_DR1, R2_USB, R5, R7, R8: ERA-1AEB3401C_CPF0201D7K68C1; ERA-1AEB3401C_0201
R_PWR_EPD: ERA-1AEB3401C_CPF0201D7K68C1; ERA-1AEB3401C_0201
R_TYPE_SEL: ERA-1AEB3401C_CPF0201D7K68C1; ERA-1AEB3401C_0201
SJ1: ESP32_C6_LIBRARY_7_JUMPER_SJ
SW_DN: 2025-10-22_07-23-44_LIBRARY_EVP-AKE31ASW_EVP-AKE3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; 2025-10-22_07-23-44_LIBRARY_SW_EVP-AKE31A_PAN
SW_ENT: 2025-10-22_07-23-44_LIBRARY_EVP-AKE31ASW_EVP-AKE3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; 2025-10-22_07-23-44_LIBRARY_SW_EVP-AKE31A_PAN
SW_UP: 2025-10-22_07-23-44_LIBRARY_EVP-AKE31ASW_EVP-AKE3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; 2025-10-22_07-23-44_LIBRARY_SW_EVP-AKE31A_PAN
TP_BAT_GND: HECTOR_WATCH_1_TPTP20R; HECTOR_WATCH_1_TP20R
TP_ON: HECTOR_WATCH_1_TPTP20R; HECTOR_WATCH_1_TP20R
TP_OP: HECTOR_WATCH_1_TPTP20R; HECTOR_WATCH_1_TP20R
TP_VBAT: HECTOR_WATCH_1_TPTP20R; HECTOR_WATCH_1_TP20R
U3: ESP32_C6_LIBRARY_MAX17048G+T10; ESP32_C6_LIBRARY_SON50P200X200X80-9N

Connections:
3V3: C34.2, IC2.C2 (VDD), Q1.2 (S), R_PWR_EPD.2; also elsewhere on the board
3V3/1.7D: R5.2, R7.2, R8.2
ALERT: U3.5 (!ALERT); also elsewhere on the board
D+: D3.4 (I/O2_2); also elsewhere on the board
D-: D3.6 (I/O1_2); also elsewhere on the board
DN: D3.1 (I/O1_1), J4.A7 (DN1), J4.B7 (DN2)
DP: D3.3 (I/O2_1), J4.A6 (DP1), J4.B6 (DP2)
EPD_3V3: C1-EP-DR.1, EPD_C5.2, J1.15, J1.16, L5.2, Q1.3 (D)
EPD_BUSY: J1.9; also elsewhere on the board
EPD_CS: J1.12; also elsewhere on the board
EPD_DC: J1.11; also elsewhere on the board
EPD_RST: J1.10; also elsewhere on the board
GDR: J1.2, Q3.1 (G), R2_EP_DR1.2
GND: C1-EP-DR.2, C27.1, C29.1, C30.1, C31.1, C32.1, C34.1, C42.1, C43.2, D3.2 (GND), D4.1 (K), EPD_C1.1, EPD_C2.1, EPD_C5.1, EPD_C6.1, EPD_C7.1, EPD_C8.1, EPD_C9.1, EPD_C10.1, EPD_C11.1, EPD_C12.1, IC2.B1 (IN/TRIG), IC2.B3 (GND), J1.8, J1.17, J1.MP1, J1.MP2, J4.A1_B12 (GND), J4.A12_B1 (GND), J4.SH1 (SHIELD), J4.SH2 (SHIELD), J4.SH3 (SHIELD), J4.SH4 (SHIELD), R1_USB.1, R2_EP_DR1.1, R2_USB.2, R_TYPE_SEL.1, SJ1.1, SW_DN.1, SW_ENT.1, SW_UP.1, TP_BAT_GND.TP, U3.1 (CTG), U3.4 (GND), U3.6 (QSTRT), U3.9 (EP); also elsewhere on the board
HAPTIC_EN: IC2.A1 (EN); also elsewhere on the board
MOSI: J1.14; also elsewhere on the board
unnamed: C2-EP-DR.2, D5.2 (A), L5.1
unnamed: C2-EP-DR.1, D2.1 (K), D4.2 (A), Q3.3 (D)
unnamed: R1_EP_DR.1, R_TYPE_SEL.2, SJ1.2
unnamed: EPD_C2.2, J1.4
unnamed: EPD_C6.2, J1.18
unnamed: EPD_C1.2, J1.5
unnamed: EPD_C7.2, J1.19
unnamed: EPD_C8.2, J1.20
unnamed: EPD_C10.2, J1.22
unnamed: EPD_C12.2, J1.24
unnamed: C32.2, IC2.A2 (REG)
unnamed: J4.A5 (CC1), R1_USB.2
unnamed: J4.B5 (CC2), R2_USB.1
OUT+: IC2.A3 (OUT+), TP_OP.TP
OUT-: IC2.C3 (OUT-), TP_ON.TP
P0.13: C30.2, R5.1, SW_UP.2; also elsewhere on the board
P0.14: C31.2, R8.1, SW_ENT.2; also elsewhere on the board
P1.01: Q1.1 (G), R_PWR_EPD.1; also elsewhere on the board
P1.02: C29.2, R7.1, SW_DN.2; also elsewhere on the board
PREVGH: D5.1 (K), EPD_C9.2, J1.21
PREVGL: D2.2 (A), EPD_C11.2, J1.23
RESE: J1.3, Q3.2 (S), R1_EP_DR.2
SCK: J1.13; also elsewhere on the board
SCL: IC2.C1 (SCL), U3.7 (SCL); also elsewhere on the board
SDA: IC2.B2 (SDA), U3.8 (SDA); also elsewhere on the board
VBAT: C27.2, TP_VBAT.TP, U3.2 (CELL), U3.3 (VDD); also elsewhere on the board
VBUS: C42.2, C43.1, D3.5 (VBUS), J4.A4_B9 (VBUS), J4.A9_B4 (VBUS); also elsewhere on the board

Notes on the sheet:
E-Paper Drive Circuit
E-Paper & Peripherals
E-Paper Display Connector
Fuel Gauge
Haptic Driver
Buttons
USB C Connector & ESD Protection

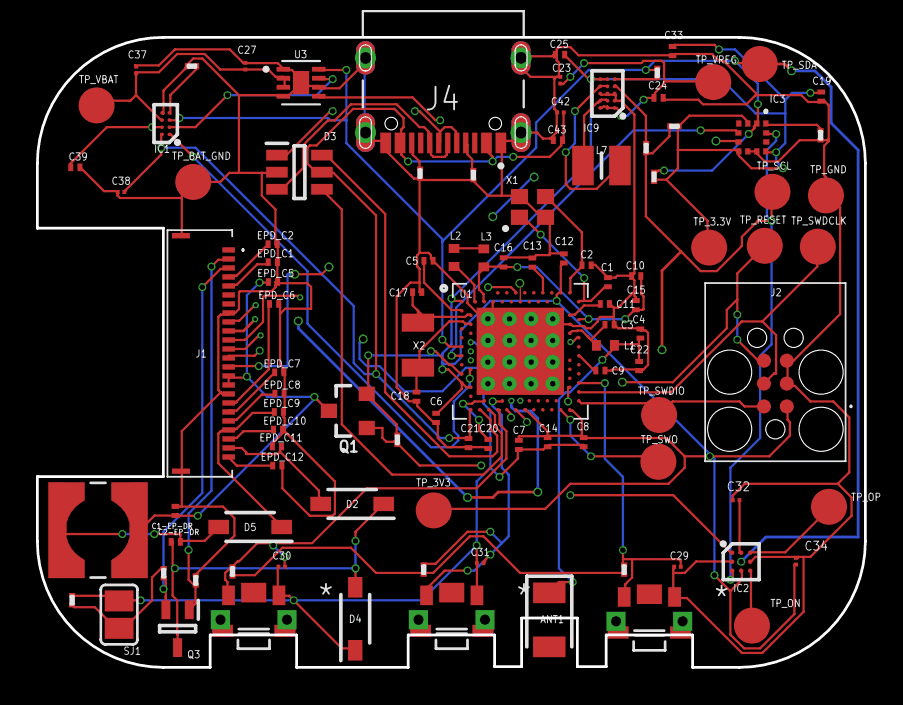
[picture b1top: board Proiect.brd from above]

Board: 4 copper layers, 46.0 x 35.0 mm, 105 parts (0 on the bottom side), 71 nets.

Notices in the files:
parts and their libraries:
COPYRIGHT: Copyright (C) 2024 Ultra Librarian. All rights reserved.
COPYRIGHT: Copyright (C) 2025 Ultra Librarian. All rights reserved.
